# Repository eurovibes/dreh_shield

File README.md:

<!-- SPDX-FileCopyrightText: 2025 Benedikt Spranger <b.spranger@linutronix.de> -->
<!-- SPDX-License-Identifier: CERN-OHL-S-2.0 -->

# dreh_shield - An Arduino Uno R3 rotary encoder input shield

dreh_shield is an Arduino Uno R3 rotary encoder input shield for two A/B
rotary encoder. It is developed to act as a companion shield to the dc_shield
(https://github.com/eurovibes/dc_shield).

## License rules

dreh_shield is provided under the terms of the CERN-OHL-S license version 2 as
provided in the LICENSES/CERN-OHL-S-2.0 file.

Instead of adding license boilerplates to the individual files, dreh_shield uses
SPDX license identifiers, which are machine parseable and considered legaly
equivalent.

The SPDX license identifier in dreh_shield shall be added at the first possible
line in a file which can contain a comment. This is normally the first line
except for scripts. Scripts require the #!PATH_TO_INTERPRETER tag in the
first line; place the SPDX identifier into the second line.

The SPDX license identifier is added in form of a comment.

## Copyright and License

Copyright Benedikt Spranger 2021.
This source describes Open Hardware and is licensed under the CERNOHL-S v2.
You may redistribute and modify this source and make products using it
under the terms of the CERN-OHL-S v2
(https://ohwr.org/cern_ohl_s_v2.txt ).
This source is distributed WITHOUT ANY EXPRESS OR IMPLIED
WARRANTY, INCLUDING OF MERCHANTABILITY, SATISFACTORY
QUALITY AND FITNESS FOR A PARTICULAR PURPOSE. Please see
the CERN-OHL-S v2 for applicable conditions.
Source location: https://github.com/eurovibes/dreh_shield
As per CERN-OHL-S v2 section 4, should You produce hardware based
on this source, You must where practicable maintain the Source Location
visible on the external case of the dreh_shield or other products you make
using this source.

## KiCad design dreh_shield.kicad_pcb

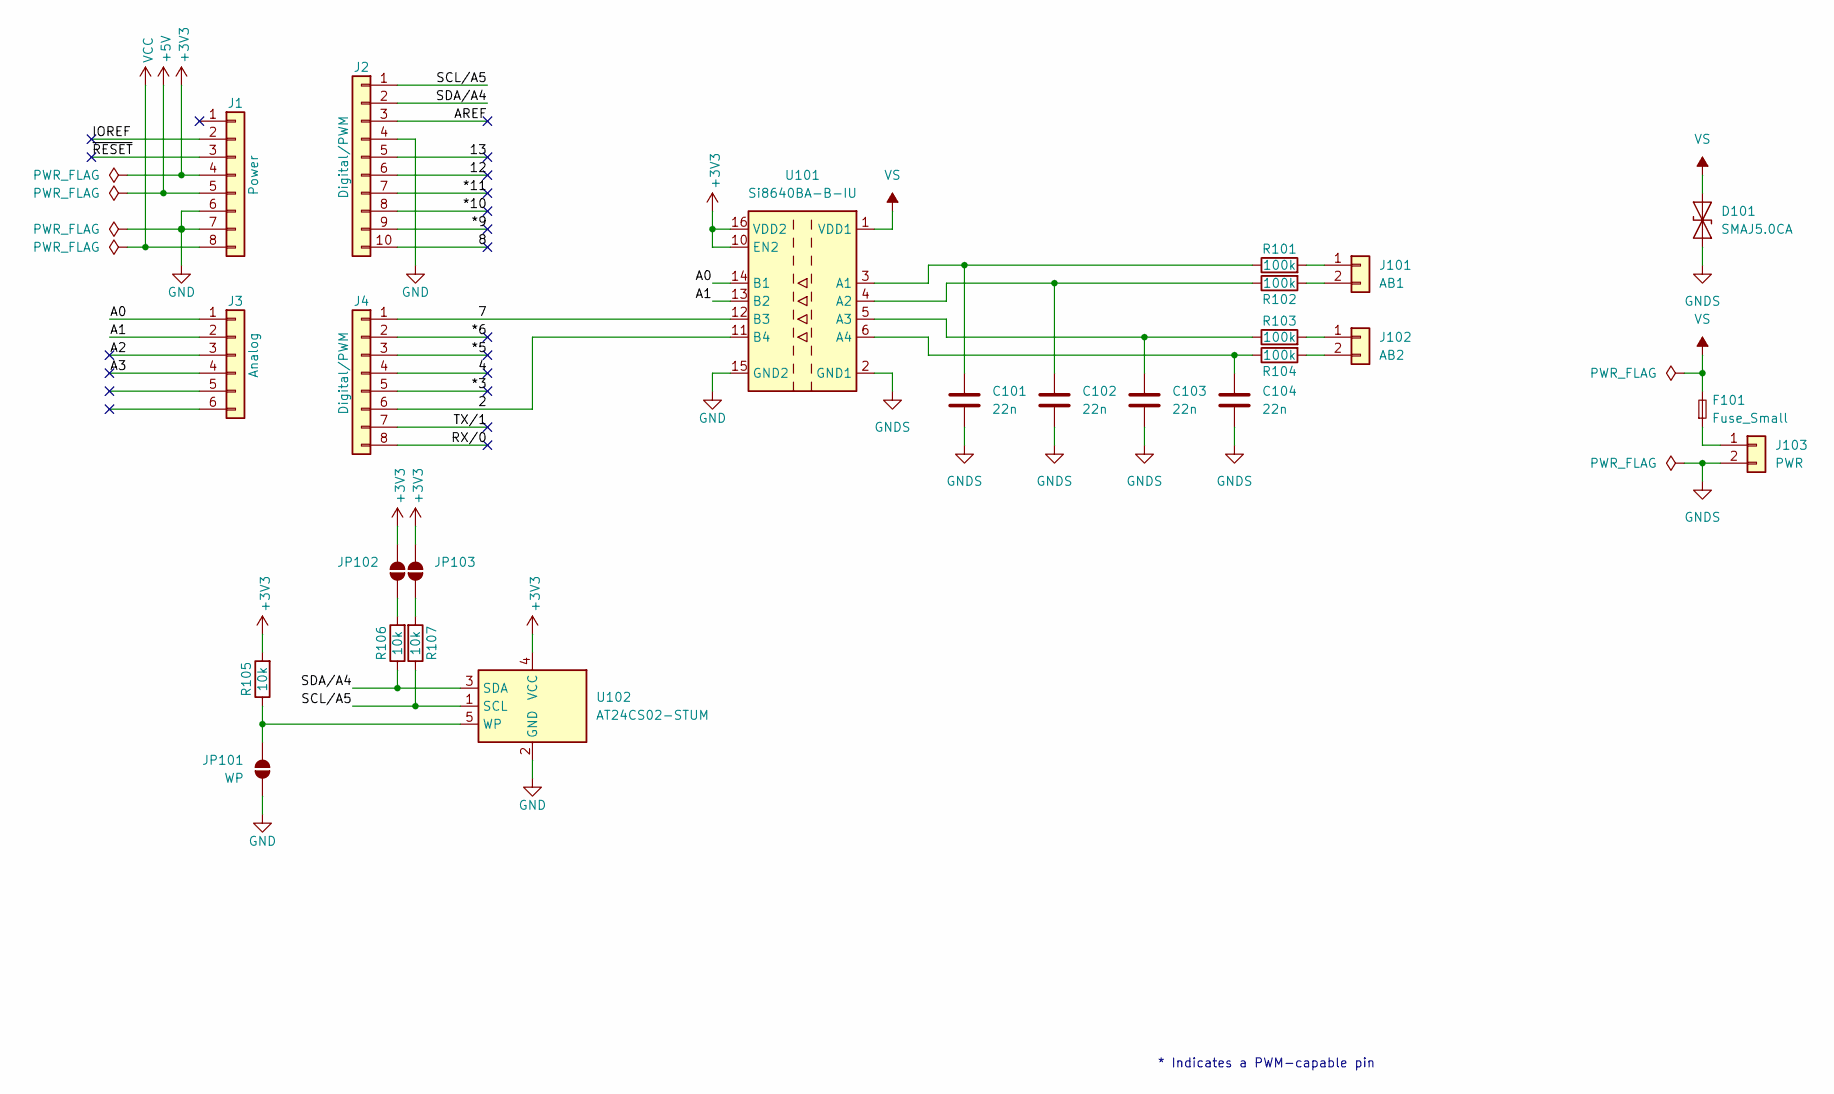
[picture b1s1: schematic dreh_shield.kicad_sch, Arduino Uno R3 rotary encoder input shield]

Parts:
C101, C102, C103, C104: 22n; C_0402_1005Metric; lcsc# C1532
D101: SMAJ5.0CA; D_SMA; lcsc# C908809
F101: Fuse_Small; Fuse_1206_3216Metric; lcsc# C70065
J1: Power; PinSocket_1x08_P2.54mm_Vertical; digikey# SAM9303-ND
J2: Digital/PWM; PinSocket_1x10_P2.54mm_Vertical; digikey# SAM15577-ND
J3: Analog; PinSocket_1x06_P2.54mm_Vertical; digikey# SAM9298-ND
J4: Digital/PWM; PinSocket_1x08_P2.54mm_Vertical; digikey# SAM9303-ND
J101: AB1; TerminalBlock_WAGO_236-402_1x02_P5.00mm_45Degree; digikey# 2946-236-402-ND
J102: AB2; TerminalBlock_WAGO_236-402_1x02_P5.00mm_45Degree; digikey# 2946-236-402-ND
J103: PWR; TerminalBlock_WAGO_236-402_1x02_P5.00mm_45Degree; digikey# 2946-236-402-ND
JP101: WP; SolderJumper-2_P1.3mm_Open_Pad1.0x1.5mm
JP102, JP103: SolderJumper-2_P1.3mm_Open_Pad1.0x1.5mm
R101, R102, R103, R104: 100k; R_0402_1005Metric; lcsc# C25741
R105, R106, R107: 10k; R_0402_1005Metric; lcsc# C25744
U101: Si8640BA-B-IU; QSOP-16_3.9x4.9mm_P0.635mm; lcsc# C52145203
U102: AT24CS02-STUM; SOT-23-5; lcsc# C5125083

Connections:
+3V3: J1.4, JP102.2 (B), JP103.2 (B), R105.2, U101.10 (EN2), U101.16 (VDD2), U102.4 (VCC)
+5V: J1.5
/2: J4.6, U101.11 (B4)
/4: J4.4
/7: J4.1, U101.12 (B3)
/8: J2.10
/12: J2.6
/13: J2.5
/*3: J4.5
/*5: J4.3
/*6: J4.2
/*9: J2.9
/*10: J2.8
/*11: J2.7
/A0: J3.1, U101.14 (B1)
/A1: J3.2, U101.13 (B2)
/A2: J3.3
/A3: J3.4
/AREF: J2.3
/IOREF: J1.2
/RX/0: J4.8
/SCL/A5: J2.1, R107.1, U102.1 (SCL)
/SDA/A4: J2.2, R106.1, U102.3 (SDA)
/TX/1: J4.7
/~RESET: J1.3
GND: J1.6, J1.7, J2.4, JP101.1 (A), U101.9 (GND2), U101.15 (GND2), U102.2 (GND)
GNDS: C101.2, C102.2, C103.2, C104.2, D101.1 (A1), J103.2, U101.2 (GND1), U101.8 (GND1)
unnamed: J101.1, R101.2
unnamed: J101.2, R102.2
unnamed: J102.1, R103.2
unnamed: J102.2, R104.2
unnamed: F101.1, J103.1
unnamed: JP101.2 (B), R105.1, U102.5 (WP)
unnamed: JP102.1 (A), R106.2
unnamed: JP103.1 (A), R107.2
unnamed: C101.1, R101.1, U101.3 (A1)
unnamed: C102.1, R102.1, U101.4 (A2)
unnamed: C103.1, R103.1, U101.5 (A3)
unnamed: C104.1, R104.1, U101.6 (A4)
VCC: J1.8
VS: D101.2 (A2), F101.2, U101.1 (VDD1)

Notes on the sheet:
* Indicates a PWM-capable pin

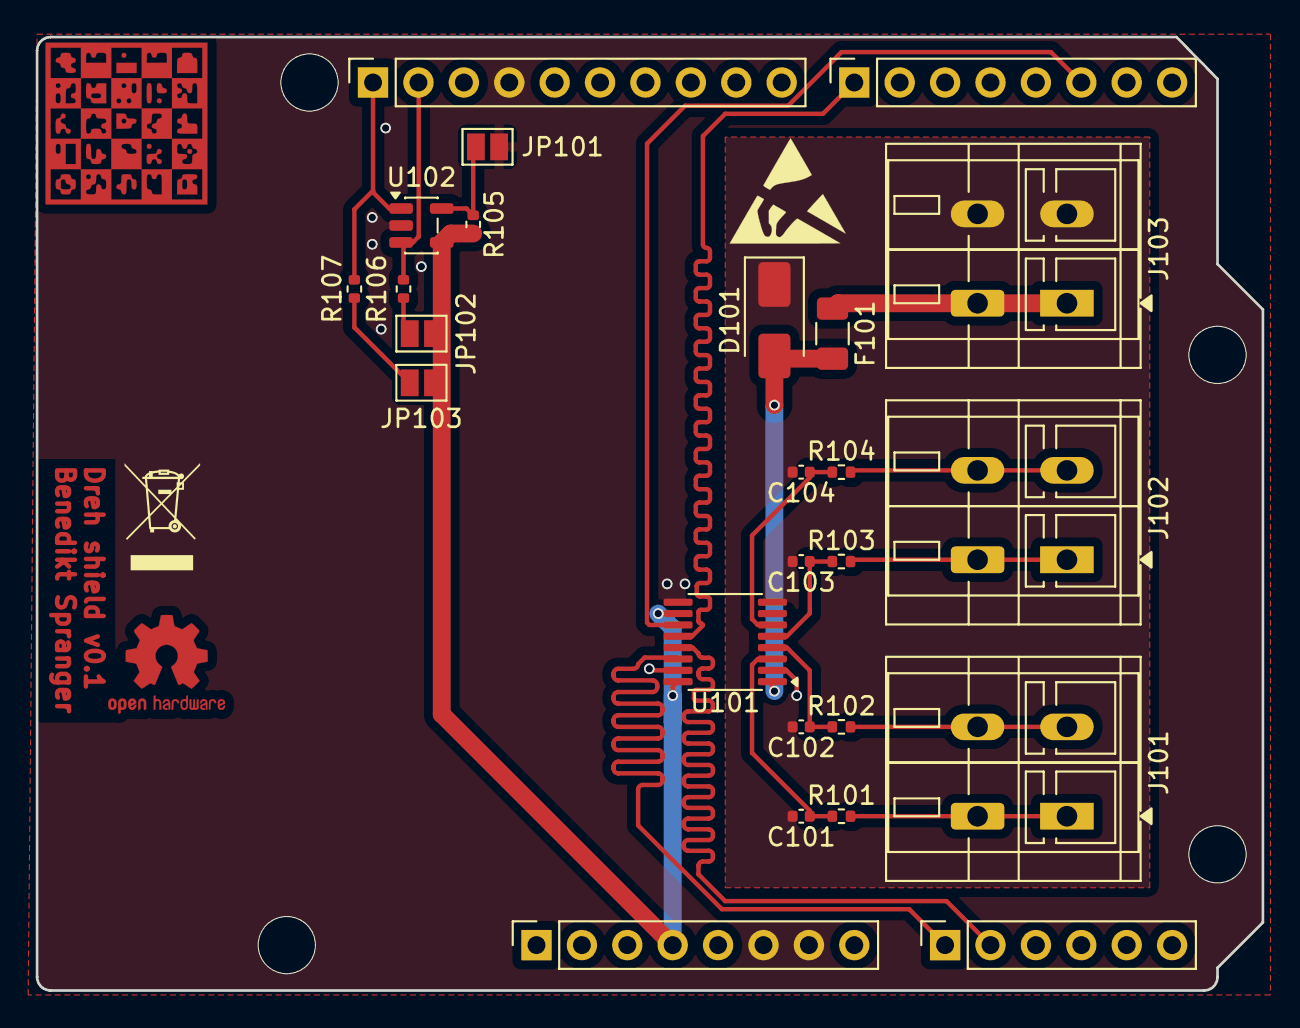
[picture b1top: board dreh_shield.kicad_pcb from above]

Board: 2 copper layers, 68.6 x 53.3 mm, 29 parts (0 on the bottom side), 22 nets.

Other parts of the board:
MH1, MH2, MH3, MH4: MountingHole_3.2mm

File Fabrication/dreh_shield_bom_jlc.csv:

"Comment","Designator","Footprint","LCSC Part #"
"22n","C101,C102,C103,C104","C_0402_1005Metric","C1532"
"SMAJ5.0CA","D101","D_SMA","C908809"
"Fuse_Small","F101","Fuse_1206_3216Metric","C70065"
"10k","R105,R106,R107","R_0402_1005Metric","C25744"
"100k","R101,R102,R103,R104","R_0402_1005Metric","C25741"
"AT24CS02-STUM","U102","SOT-23-5","C5125083"
"Si8640BA-B-IU","U101","QSOP-16_3.9x4.9mm_P0.635mm","C52145203"

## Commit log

2025-12-14 Initial gh-pages commit
2025-12-14 Deploying to gh-pages from @ eurovibes/dreh_shield@c855f83a3ce4c837dadbc48d59febe4bcd6b068e 🚀
2025-12-14 Deploying to gh-pages from @ eurovibes/dreh_shield@908c83415b76ab9cc0bed0690fc798ffe1b68563 🚀
2025-12-15 Add github CI/CD action
2025-12-15 Add Logo
2025-12-15 Initial
2025-12-15 Deploying to gh-pages from @ eurovibes/dreh_shield@ddd7d17db12d1d3c62c75617f01a7b7efe5b7392 🚀

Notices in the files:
dreh_shield.kicad_pcb:
This work is licensed under the CERN-OHL-S v2
